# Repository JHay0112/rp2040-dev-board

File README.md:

# RP2040 Dev. Board

This repository contains a development board design for the RP2040 loosely 
based around the Pi Pico. 

The goal of this design was to produce a development board for a common 
microcontroller for the purpose of demonstrating a simple PCB design. The 
design had to be breadboard compatible and use USB-C for programming. 

The designed board (as shown below) fulfills all of these requirements.

The board was manufactured and assembled by JLCPCB, and used to blink an LED
to demonstrate it is in working condition (shown below).

The design of the board could be improved by increasing pin count and 
reducing the width of the PCB to allow more room for breadboarding around
the board.

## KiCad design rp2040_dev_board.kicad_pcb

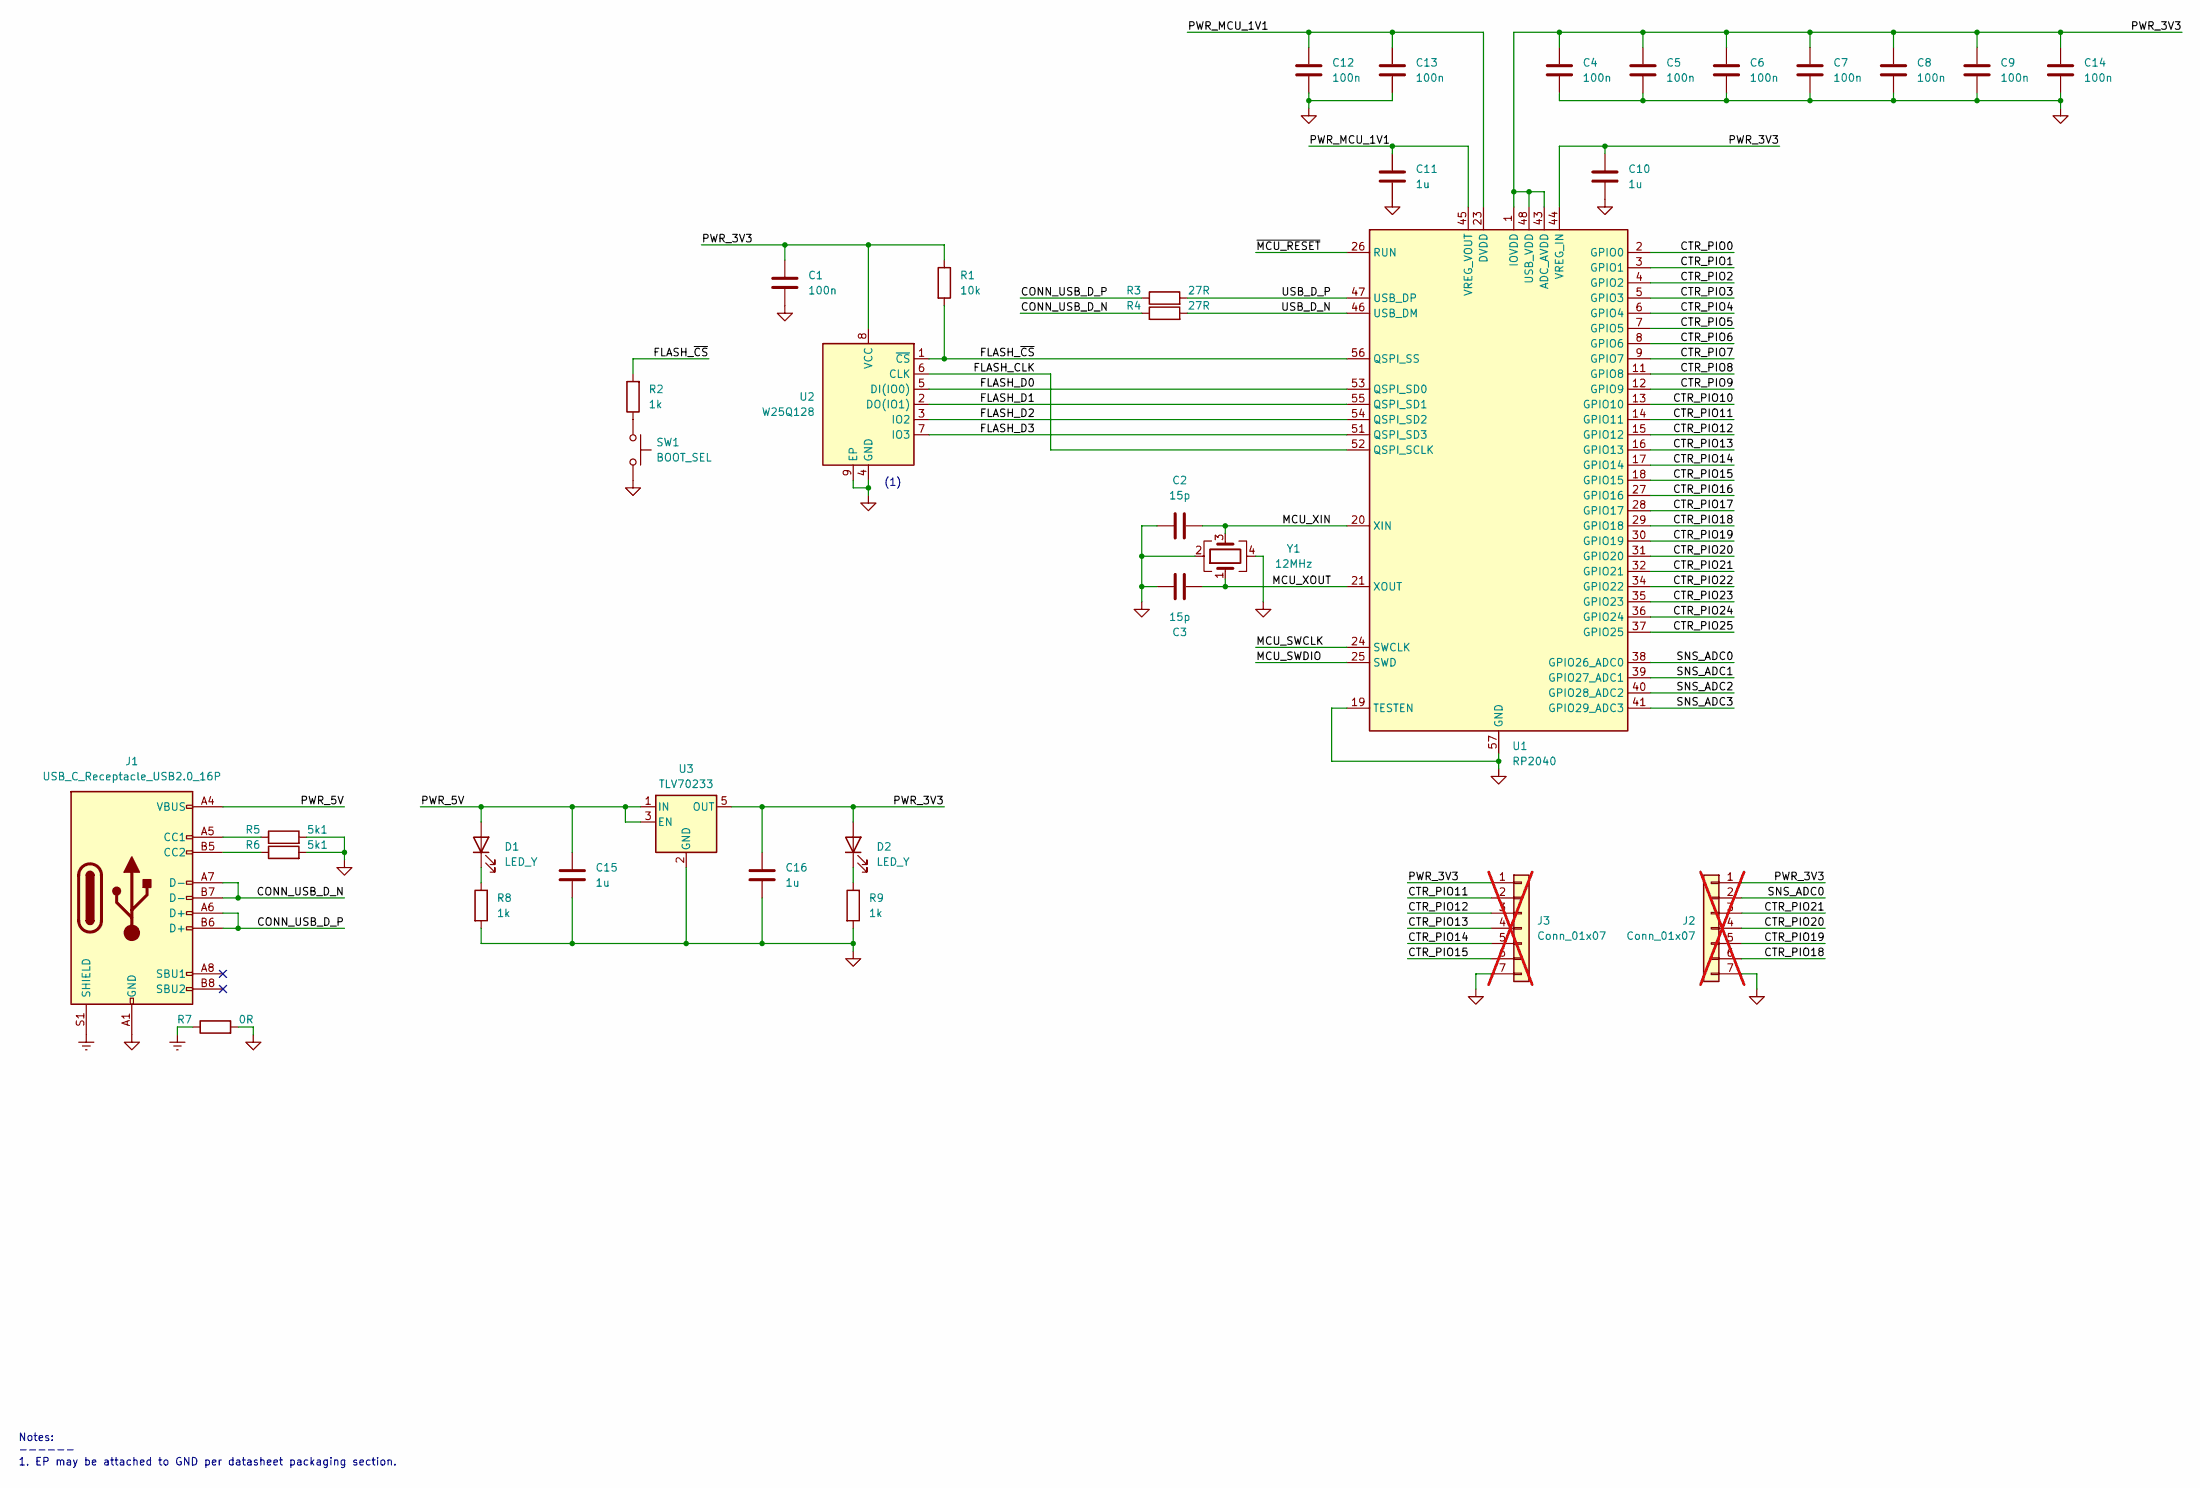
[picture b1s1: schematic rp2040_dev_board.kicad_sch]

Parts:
C1, C4, C5, C6, C7, C8, C9, C12, C13, C14: 100n; C_0603_1608Metric; Manufacturer PN CC0603KRX7R9BB104
C2, C3: 15p; C_0603_1608Metric; Manufacturer PN CL10C150JB8NNNC
C10, C11, C15, C16: 1u; C_0603_1608Metric; Manufacturer PN CC0603KRX7R9BB105
D1, D2: LED_Y; LED_0603_1608Metric; Manufacturer PN 19-213/Y2C-CQ2R2L/3T(CY)
J1: USB_C_Receptacle_USB2.0_16P; USB_C_Receptacle_GCT_USB4105-xx-A_16P_TopMnt_Horizontal; Manufacturer PN GT-USB-7004N
J2, J3: Conn_01x07; PinHeader_1x07_P2.54mm_Vertical; not fitted
R1: 10k; R_0603_1608Metric; Manufacturer PN 0603WAF1002T5E
R2, R8, R9: 1k; R_0603_1608Metric; Manufacturer PN 0603WAF1001T5E
R3, R4: 27R; R_0603_1608Metric; Manufacturer PN 0603WAF270JT5E
R5, R6: 5k1; R_0603_1608Metric; Manufacturer PN 0603WAF5101T5E
R7: 0R; R_0603_1608Metric; Manufacturer PN 0603WAF0000T5E
SW1: BOOT_SEL; SW_SPST_PTS810; Manufacturer PN TSA016A2518C
U1: RP2040; QFN-56-1EP_7x7mm_P0.4mm_EP3.2x3.2mm; Manufacturer PN RP2040
U2: W25Q128; WSON-8-1EP_6x5mm_P1.27mm_EP3.4x4.3mm; Manufacturer PN W25Q128JVPIQ
U3: TLV70233; SOT-23-5; Manufacturer PN TLV70233DBVR
Y1: 12MHz; Crystal_SMD_Abracon_ABM8AIG-4Pin_3.2x2.5mm; Manufacturer PN ABM8-272-T3

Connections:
/CONN_USB_D_N: J1.A7 (D-), J1.B7 (D-), R4.1
/CONN_USB_D_P: J1.A6 (D+), J1.B6 (D+), R3.1
/CTR_PIO0: U1.2 (GPIO0)
/CTR_PIO1: U1.3 (GPIO1)
/CTR_PIO2: U1.4 (GPIO2)
/CTR_PIO3: U1.5 (GPIO3)
/CTR_PIO4: U1.6 (GPIO4)
/CTR_PIO5: U1.7 (GPIO5)
/CTR_PIO6: U1.8 (GPIO6)
/CTR_PIO7: U1.9 (GPIO7)
/CTR_PIO8: U1.11 (GPIO8)
/CTR_PIO9: U1.12 (GPIO9)
/CTR_PIO10: U1.13 (GPIO10)
/CTR_PIO11: J3.2, U1.14 (GPIO11)
/CTR_PIO12: J3.3, U1.15 (GPIO12)
/CTR_PIO13: J3.4, U1.16 (GPIO13)
/CTR_PIO14: J3.5, U1.17 (GPIO14)
/CTR_PIO15: J3.6, U1.18 (GPIO15)
/CTR_PIO16: U1.27 (GPIO16)
/CTR_PIO17: U1.28 (GPIO17)
/CTR_PIO18: J2.6, U1.29 (GPIO18)
/CTR_PIO19: J2.5, U1.30 (GPIO19)
/CTR_PIO20: J2.4, U1.31 (GPIO20)
/CTR_PIO21: J2.3, U1.32 (GPIO21)
/CTR_PIO22: U1.34 (GPIO22)
/CTR_PIO23: U1.35 (GPIO23)
/CTR_PIO24: U1.36 (GPIO24)
/CTR_PIO25: U1.37 (GPIO25)
/FLASH_CLK: U1.52 (QSPI_SCLK), U2.6 (CLK)
/FLASH_D0: U1.53 (QSPI_SD0), U2.5 (DI(IO0))
/FLASH_D1: U1.55 (QSPI_SD1), U2.2 (DO(IO1))
/FLASH_D2: U1.54 (QSPI_SD2), U2.3 (IO2)
/FLASH_D3: U1.51 (QSPI_SD3), U2.7 (IO3)
/FLASH_~CS: R1.2, R2.2, U1.56 (QSPI_SS), U2.1 (~CS)
/MCU_SWCLK: U1.24 (SWCLK)
/MCU_SWDIO: U1.25 (SWD)
/MCU_XIN: C2.2, U1.20 (XIN), Y1.3
/MCU_XOUT: C3.2, U1.21 (XOUT), Y1.1
/PWR_3V3: C1.1, C4.1, C5.1, C6.1, C7.1, C8.1, C9.1, C10.1, C14.1, C16.1, D2.2 (A), J2.1, J3.1, R1.1, U1.1 (IOVDD), U1.10 (IOVDD), U1.22 (IOVDD), U1.33 (IOVDD), U1.42 (IOVDD), U1.43 (ADC_AVDD), U1.44 (VREG_IN), U1.48 (USB_VDD), U1.49 (IOVDD), U2.8 (VCC), U3.5 (OUT)
/PWR_5V: C15.1, D1.2 (A), J1.A4 (VBUS), J1.A9 (VBUS), J1.B4 (VBUS), J1.B9 (VBUS), U3.1 (IN), U3.3 (EN)
/PWR_MCU_1V1: C11.1, C12.1, C13.1, U1.23 (DVDD), U1.45 (VREG_VOUT), U1.50 (DVDD)
/SNS_ADC0: J2.2, U1.38 (GPIO26_ADC0)
/SNS_ADC1: U1.39 (GPIO27_ADC1)
/SNS_ADC2: U1.40 (GPIO28_ADC2)
/SNS_ADC3: U1.41 (GPIO29_ADC3)
/USB_D_N: R4.2, U1.46 (USB_DM)
/USB_D_P: R3.2, U1.47 (USB_DP)
/~MCU_RESET: U1.26 (RUN)
Earth: J1.S1 (SHIELD), R7.1
GND: C1.2, C2.1, C3.1, C4.2, C5.2, C6.2, C7.2, C8.2, C9.2, C10.2, C11.2, C12.2, C13.2, C14.2, C15.2, C16.2, J1.A1 (GND), J1.A12 (GND), J1.B1 (GND), J1.B12 (GND), J2.7, J3.7, R5.2, R6.2, R7.2, R8.2, R9.2, SW1.2, U1.19 (TESTEN), U1.57 (GND), U2.4 (GND), U2.9 (EP), U3.2 (GND), Y1.2, Y1.4
unnamed: D1.1 (K), R8.1
unnamed: D2.1 (K), R9.1
unnamed: J1.A5 (CC1), R5.1
unnamed: J1.B5 (CC2), R6.1
unnamed: R2.1, SW1.1

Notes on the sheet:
Notes: ------ 1. EP may be attached to GND per datasheet packaging section.
(1)

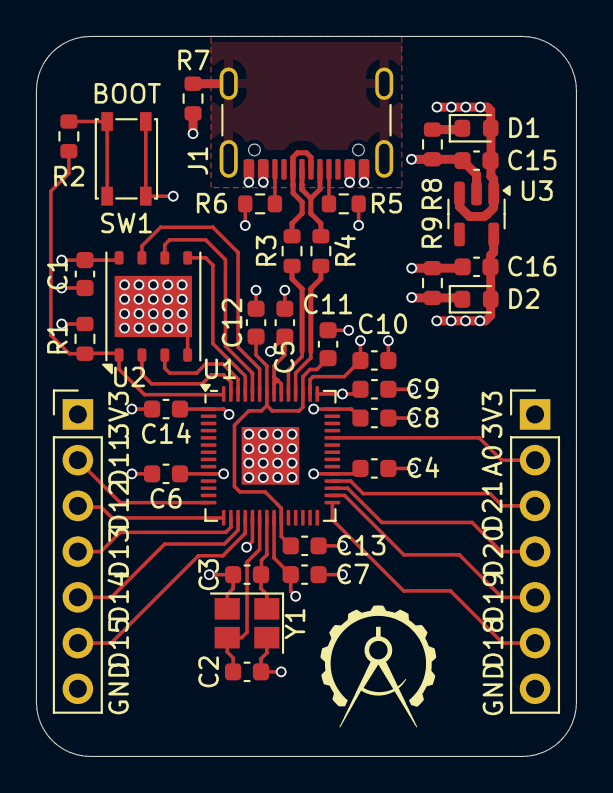
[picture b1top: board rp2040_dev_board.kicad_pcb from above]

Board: 4 copper layers, 30.0 x 40.0 mm, 35 parts (0 on the bottom side), 32 nets.

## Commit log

2024-06-10 Initial design of RP2040 development board
